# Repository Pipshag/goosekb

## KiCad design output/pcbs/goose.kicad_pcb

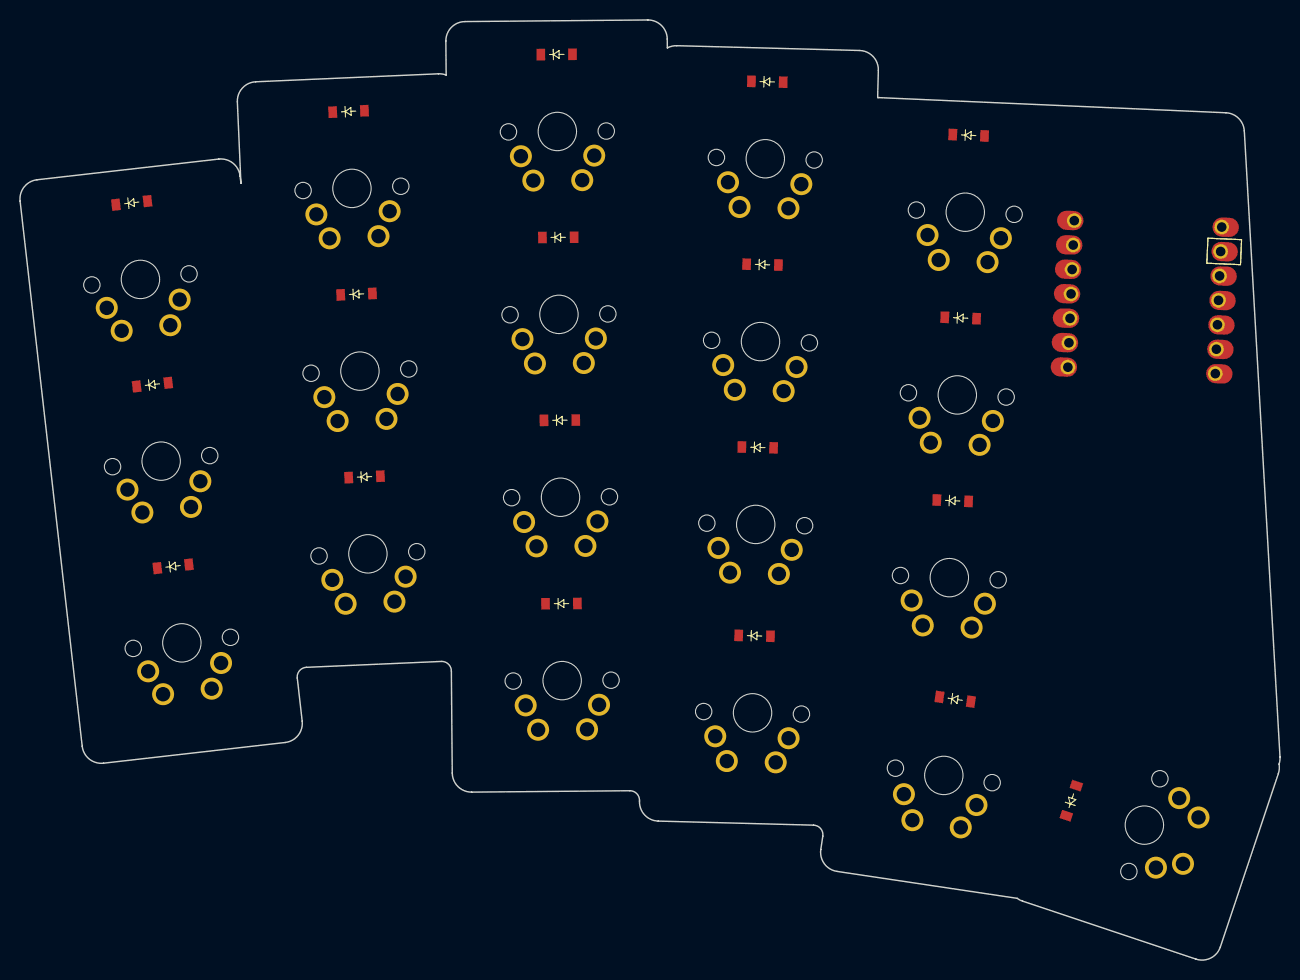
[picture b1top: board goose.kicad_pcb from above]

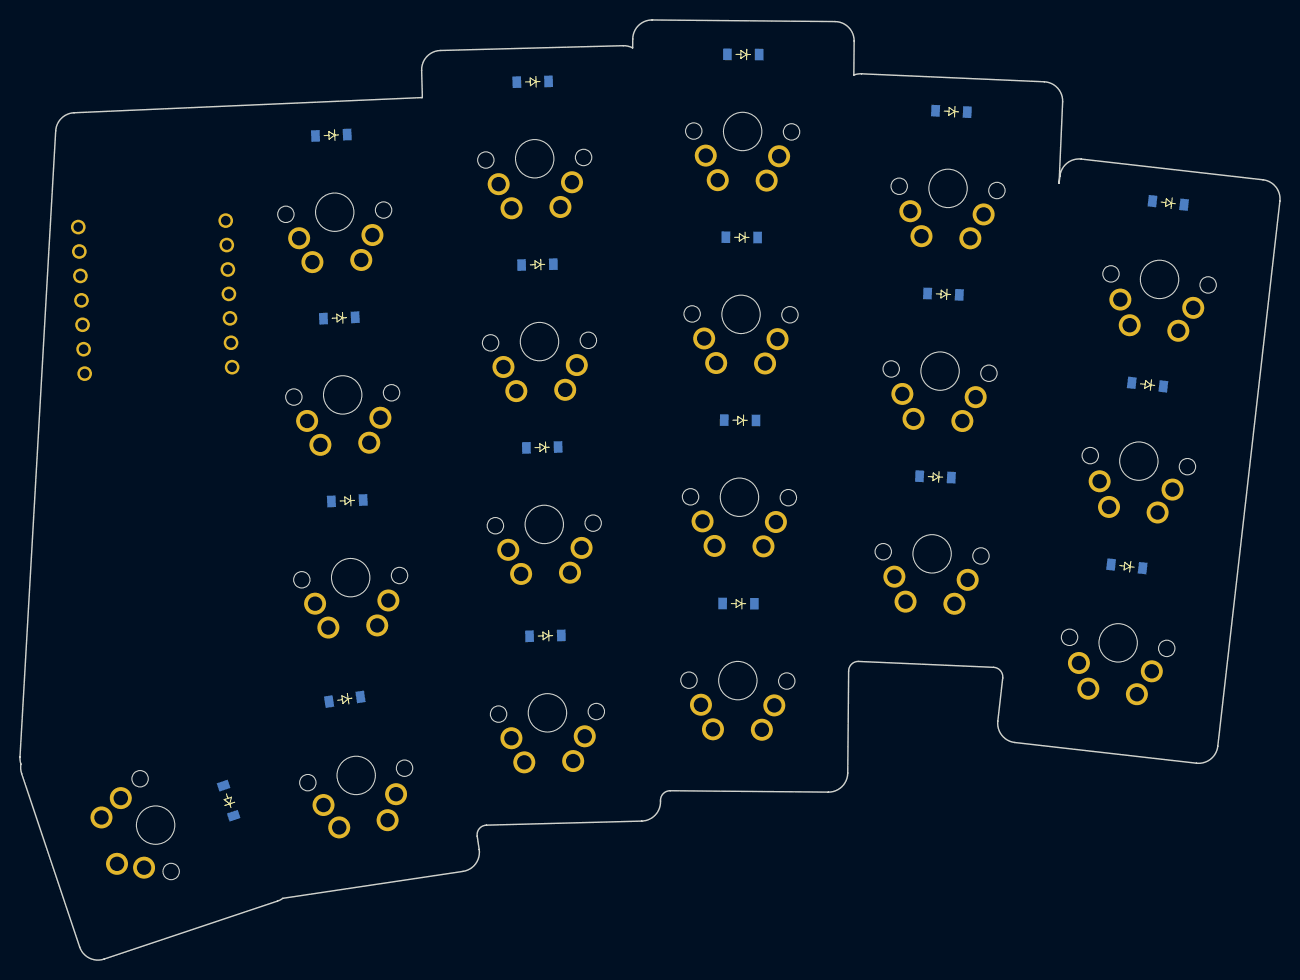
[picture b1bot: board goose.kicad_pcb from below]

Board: 2 copper layers, 130.9 x 97.7 mm, 39 parts (19 on the bottom side), 19 nets, no tracks yet.

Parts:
D1, D2, D3, D4, D5, D6, D7, D8, D9, D10, D11, D12, D13, D14, D15, D16, D17, D18, D19: ComboDiode
MCU1: Seeeduino XIAO-MOUDLE14P-2.54-21X17.8MM tht maybe
S1, S2, S3, S4, S5, S6, S7, S8, S9, S10, S11, S12, S13, S14, S15, S16, S17, S18, S19: MX

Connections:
index_bottom: D10.2, S10.2
index_home: D11.2, S11.2
index_top: D12.2, S12.2
inner_bottom: D13.2, S13.2
inner_home: D14.2, S14.2
inner_thumbs: D17.2, S17.2
inner_top: D15.2, S15.2
middle_bottom: D7.2, S7.2
middle_home: D8.2, S8.2
middle_thumbs: D16.2, S16.2
middle_top: D9.2, S9.2
outer_thumbs: D18.2, S18.2
pinkie_bottom: D1.2, S1.2
pinkie_home: D2.2, S2.2
pinkie_top: D3.2, S3.2
reach_thumbs: D19.2, S19.2
ring_bottom: D4.2, S4.2
ring_home: D5.2, S5.2
ring_top: D6.2, S6.2
